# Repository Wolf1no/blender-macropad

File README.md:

# Blender Macropad

Custom 12 key macropad with rotary encoder and OLED display, designed for better Blender workflow. Made for Half Life PCB project.

## What is this

I am learning Blender and I have a TKL keyboard (no numpad), so viewport navigation is painful. This macropad gives me numpad keys (0-9, dot, enter) for viewport shortcuts, a rotary encoder for zooming/volume control and an OLED display for showing playing audio/telemetry

## Hardware

- 12x Cherry MX compatible switches in 4x3 grid
- EC11 rotary encoder with push button
- 2.08" SH1122 OLED display (SPI)
- Pro Micro RP2040 (TENSTAR clone, mounted on back side, parts facing out)
- 3D printed case (designed separately)

## How it works

Keys are wired in a 4x3 matrix with 1N4148 diodes which prevents ghosting (details in JOURNAL.md). The Pro Micro scans rows and columns to detect which key is pressed. Encoder uses two signal lines with 10k pullup resistors. OLED connects over SPI (5 pins).

Firmware runs KMK (keyboard focused layer). Bindings are fully customizable in code.py. OLED driver for SH1122 is not yet available in KMK, commented out in code for now.

## Board

- Size: 98 x 99.2mm (2 layer, under JLCPCB 100x100 cheap limit)
- 4x M3 mounting holes
- Pro Micro USB-C aligns with top edge
- Diode direction: ROW2COL

## Pin mapping

- Rows: GP2, GP3, GP4
- Columns: GP5, GP6, GP7, GP8
- Encoder: GP27 (A), GP28 (B), GP29 (click)
- OLED: GP22 (CLK), GP23 (MOSI), GP21 (CS), GP20 (DC), GP26 (RST)
- Power: 3V3 to VCC, all GND to GND

## Build

1. Order PCB from JLCPCB using gerber files in /gerbers
2. Solder diodes, resistors, MX switches, encoder, pin headers
3. Mount Pro Micro on back side (parts facing out, check TX0/RAW marking on silkscreen)
4. Flash CircuitPython on Pro Micro RP2040
5. Copy code.py and KMK library to the board
6. Print case (STL in /case when available)

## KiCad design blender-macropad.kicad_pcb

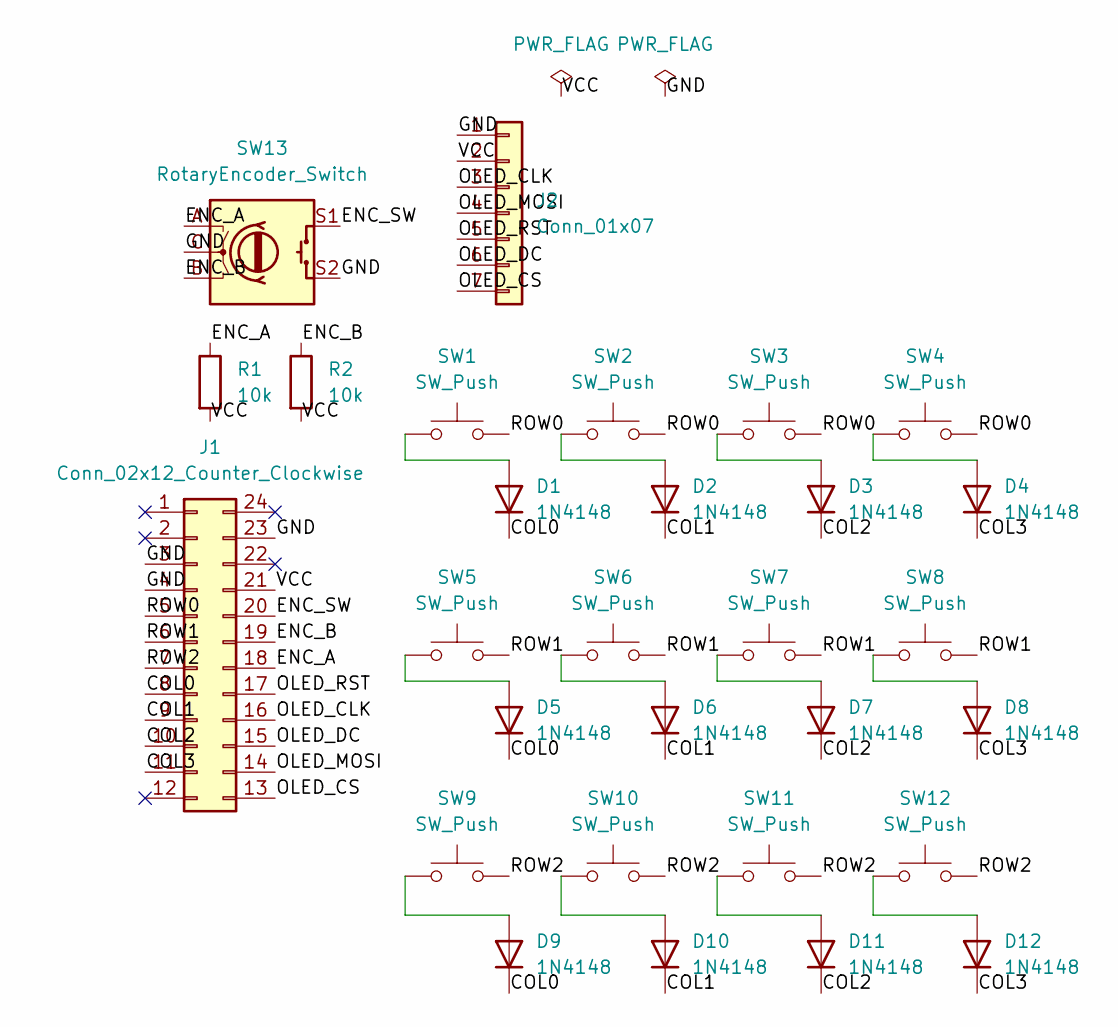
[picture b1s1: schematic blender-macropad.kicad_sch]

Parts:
D1, D2, D3, D4, D5, D6, D7, D8, D9, D10, D11, D12: 1N4148; D_DO-35_SOD27_P7.62mm_Horizontal
J1: Conn_02x12_Counter_Clockwise; DIP-24_W15.24mm
J2: Conn_01x07; PinHeader_1x07_P2.54mm_Vertical
R1, R2: 10k; R_0805_2012Metric
SW1, SW2, SW3, SW4, SW5, SW6, SW7, SW8, SW9, SW10, SW11, SW12: SW_Push; SW_Cherry_MX_1.00u_PCB
SW13: RotaryEncoder_Switch; RotaryEncoder_Alps_EC11E-Switch_Vertical_H20mm

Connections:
/COL0: D1.1 (K), D5.1 (K), D9.1 (K), J1.8
/COL1: D2.1 (K), D6.1 (K), D10.1 (K), J1.9
/COL2: D3.1 (K), D7.1 (K), D11.1 (K), J1.10
/COL3: D4.1 (K), D8.1 (K), D12.1 (K), J1.11
/ENC_A: J1.18, R1.1, SW13.A
/ENC_B: J1.19, R2.1, SW13.B
/ENC_SW: J1.20, SW13.S1
/GND: J1.3, J1.4, J1.23, J2.1, SW13.C, SW13.S2
/OLED_CLK: J1.16, J2.3
/OLED_CS: J1.13, J2.7
/OLED_DC: J1.15, J2.6
/OLED_MOSI: J1.14, J2.4
/OLED_RST: J1.17, J2.5
/ROW0: J1.5, SW1.2, SW2.2, SW3.2, SW4.2
/ROW1: J1.6, SW5.2, SW6.2, SW7.2, SW8.2
/ROW2: J1.7, SW9.2, SW10.2, SW11.2, SW12.2
/VCC: J1.21, J2.2, R1.2, R2.2
unnamed: D1.2 (A), SW1.1
unnamed: D2.2 (A), SW2.1
unnamed: D3.2 (A), SW3.1
unnamed: D4.2 (A), SW4.1
unnamed: D5.2 (A), SW5.1
unnamed: D6.2 (A), SW6.1
unnamed: D7.2 (A), SW7.1
unnamed: D8.2 (A), SW8.1
unnamed: D9.2 (A), SW9.1
unnamed: D10.2 (A), SW10.1
unnamed: D11.2 (A), SW11.1
unnamed: D12.2 (A), SW12.1

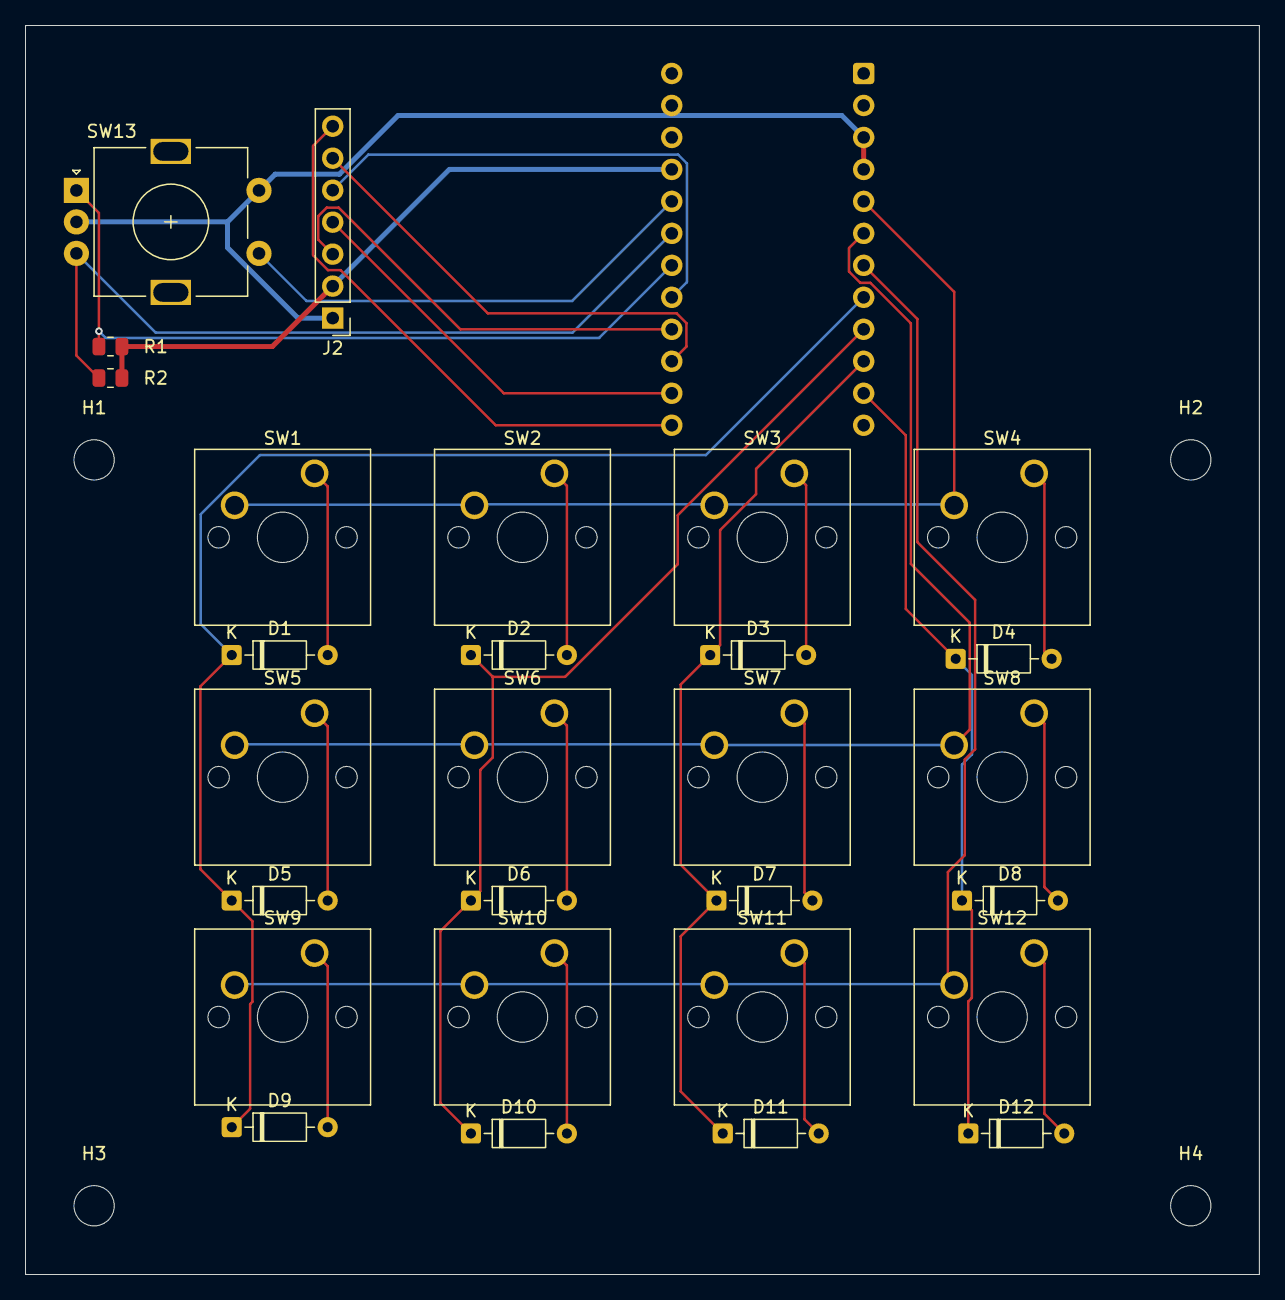
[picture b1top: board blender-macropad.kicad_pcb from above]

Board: 2 copper layers, 98.0 x 99.2 mm, 33 parts (1 on the bottom side), 29 nets.

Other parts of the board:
H1, H2, H3, H4: M3; MountingHole_3.2mm_M3
